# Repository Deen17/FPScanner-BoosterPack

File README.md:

# CCS Code for the FPScanner
For use with a GT-521FXX Fingerprint Scanner. 

This project contains library code for the fingerprint scanner, compatible with TI LaunchPad devices. To follow along with the entire design of the project, check out https://www.hackster.io/adilr3/fpscanner-boosterpack-739ad2.

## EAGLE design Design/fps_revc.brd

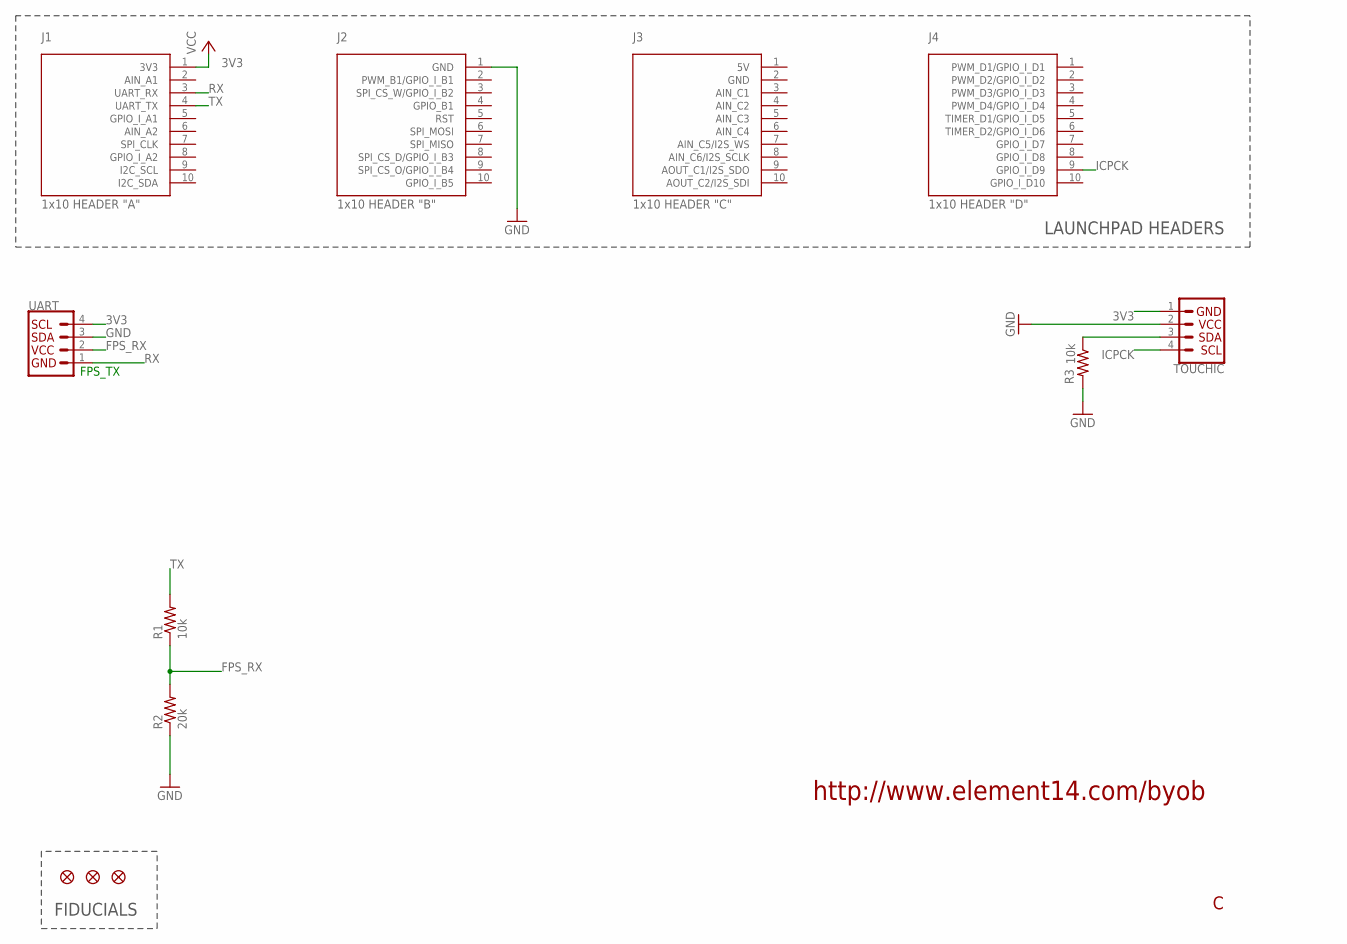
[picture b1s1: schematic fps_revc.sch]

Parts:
FID1, FID2, FID3: FIDUCIAL; FIDUCIAL_L10
J1: 1x10 HEADER "A"; 1X10; MPN SSW-110-23-F-D
J2: 1x10 HEADER "B"; 1X10; MPN SSW-110-23-F-D
J3: 1x10 HEADER "C"; 1X10
J4: 1x10 HEADER "D"; 1X10
R1, R3: 10k; R0805; MPN ERJ6GEYJ103V
R2: 20k; R0805; MPN CRCW080520K0FKEB
TOUCHIC: QWIIC_CONNECTORJS-1MM; 1X04_1MM_RA; MPN SM04B-SRSS-TB(LF)(SN)
UART: QWIIC_CONNECTORJS-1MM; 1X04_1MM_RA; MPN SM04B-SRSS-TB(LF)(SN)

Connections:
3V3: J1.1 (3V3), TOUCHIC.1 (GND), UART.4 (SCL)
FPS_RX: R1.1, R2.2, UART.2 (VCC)
GND: J2.1 (GND), R2.1, R3.2, TOUCHIC.2 (VCC), UART.3 (SDA)
ICPCK: J4.9 (GPIO_I_D9), TOUCHIC.4 (SCL)
unnamed: R3.1, TOUCHIC.3 (SDA)
RX: J1.3 (UART_RX), UART.1 (GND)
TX: J1.4 (UART_TX), R1.2

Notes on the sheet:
LAUNCHPAD HEADERS
FIDUCIALS
http://www.element14.com/byob
FPS_TX

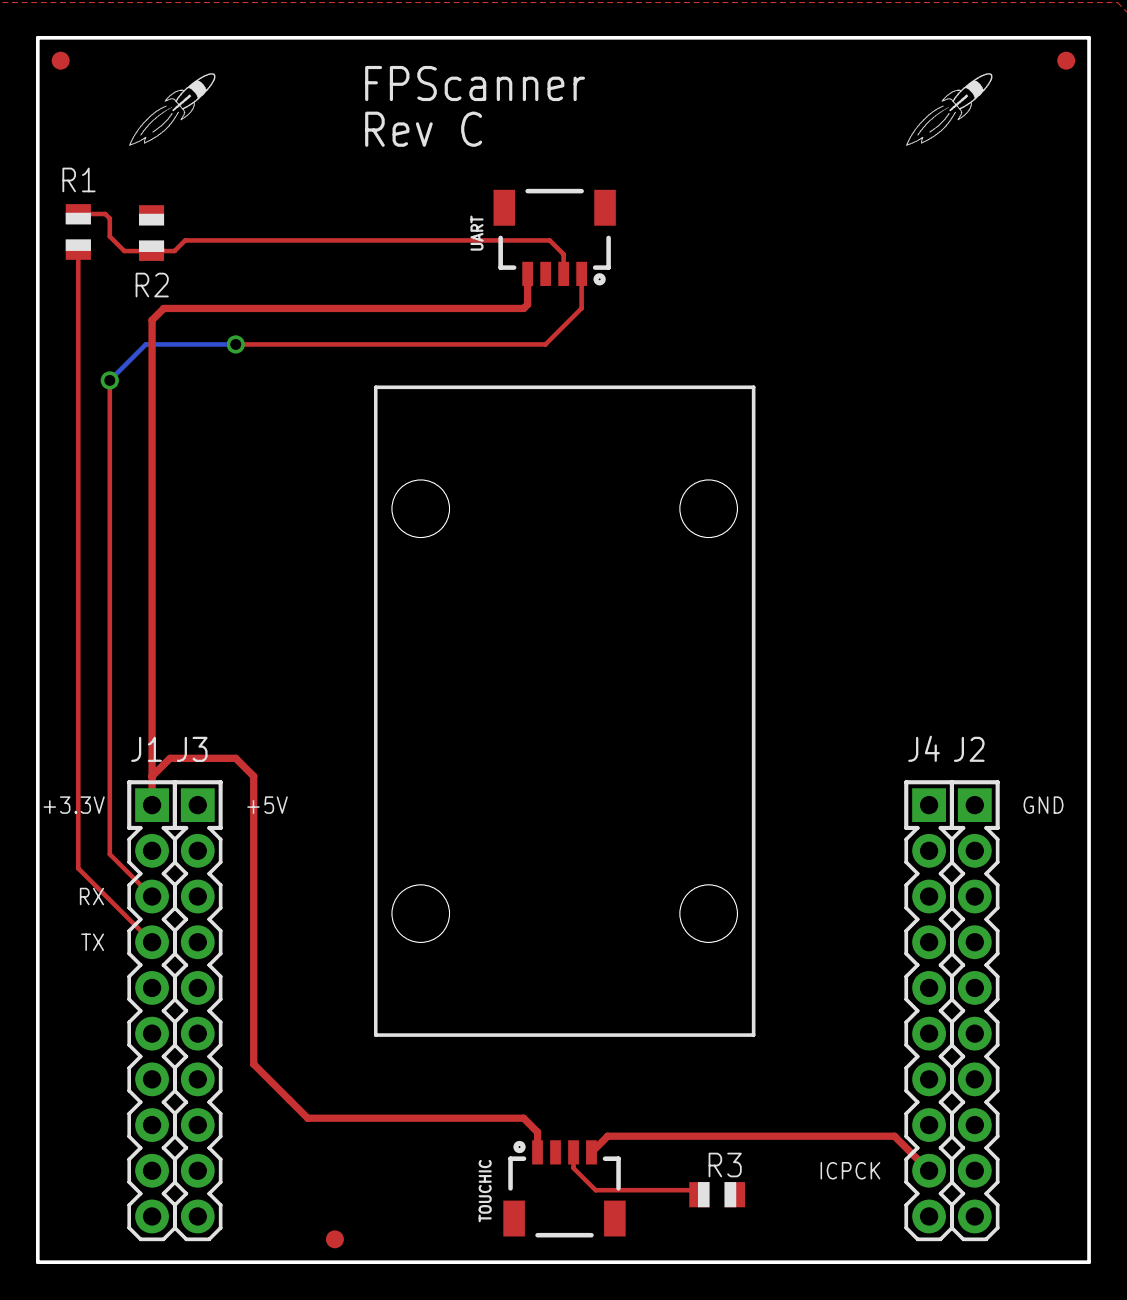
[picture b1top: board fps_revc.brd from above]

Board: 2 copper layers, 58.4 x 68.0 mm, 14 parts (0 on the bottom side), 7 nets.

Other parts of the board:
U$1, U$2: LOGO-ROCKET

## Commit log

2021-03-17 fps_uart library addition, payload construction of data/response packets
2021-03-17 Need to figure out how to communicate with UART via pins, not via USB
2021-03-17 fixed expected_checksum, changed sleep lengths, prob need to add a clock
2021-03-19 1st working set of code for fingerprint scanner
    fps.h: devinfo struct, data start code
    fps_cmd.c: corrected && to & operator
    for checksum & payload func
    fps_uart/c: fps_check_usb,
    fps_open_info
2021-03-19 documentation and status checking on fps_aurt.h
2021-03-19 add fps functions to fps.h
2021-04-04 little more uart work
2021-04-05 changed some functions to return `result` structs instead of just an integer to provide extra info
2021-04-29 various bugfixes, testing enrollment/identification
2021-05-01 working identification and enrollment!!!!!!
2021-05-01 clarity in enrollment success vs verification success in LEDs
2021-05-02 semaphore start
2021-05-02 revert to working code
2021-05-07 restructuring, includes design files
2021-05-07 README move to base

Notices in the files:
parts and their libraries:
SparkFun-Connectors: Licensing: Creative Commons ShareAlike 4.0 International - https://creativecommons.org/licenses/by-sa/4.0
